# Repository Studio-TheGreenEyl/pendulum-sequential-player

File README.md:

# pendulum-sequential-player
for the exhibition "[sound] / [laut]" at Humboldt Box 2018

22 Pendulums running autonomously or in a simple network

- Processing 3 running on Raspberry Pi 3
- oscP5 library
- controlP5 library
- Processing I/O library

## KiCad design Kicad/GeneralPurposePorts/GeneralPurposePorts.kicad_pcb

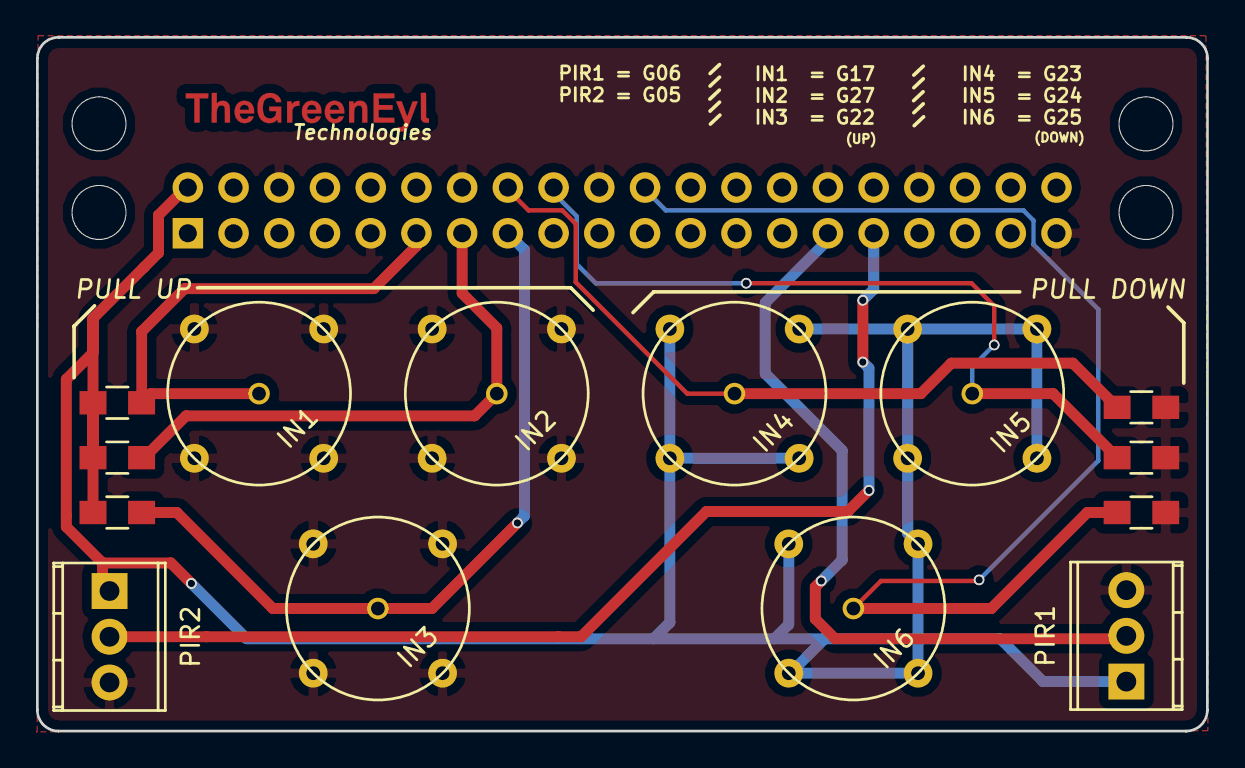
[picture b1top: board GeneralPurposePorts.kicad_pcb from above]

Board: 2 copper layers, 65.0 x 38.5 mm, 15 parts (1 on the bottom side), 11 nets.

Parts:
IN1, IN2, IN3, IN4, IN5, IN6: RCAUpright; JEITA_RCA
J2: Conn_02x20_Odd_Even; Socket_Strip_Straight_2x20_Pitch2.54mm
PIR1, PIR2: Screw_Terminal_01x03; TerminalBlock_Pheonix_MPT-2.54mm_3pol
R1, R2, R3, R4, R5, R6: 10k; R_0805_HandSoldering

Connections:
3.3V: J2.1, J2.17
5V: IN4.1, IN4.2, IN4.3, IN4.4, IN5.1, IN5.2, IN5.3, IN5.4, IN6.1, IN6.2, IN6.3, IN6.4, J2.2, PIR1.1, PIR2.1, R1.2, R2.2, R3.2
/IN1: IN1.5, J2.11, R1.1
/IN2: IN2.5, J2.13, R2.1
/IN3: IN3.5, J2.15, R3.1
/IN4: IN4.5, J2.16, R4.1
/IN5: IN5.5, J2.18, R5.1
/IN6: IN6.5, J2.22, R6.1
/PIR: J2.29, PIR1.2
/PIR2: J2.31, PIR2.2
GND: IN1.1, IN1.2, IN1.3, IN1.4, IN2.1, IN2.2, IN2.3, IN2.4, IN3.1, IN3.2, IN3.3, IN3.4, J2.6, J2.9, J2.14, J2.20, J2.25, J2.30, J2.34, J2.39, PIR1.3, PIR2.3, R4.2, R5.2, R6.2

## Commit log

2020-03-11 init
